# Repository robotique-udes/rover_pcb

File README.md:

# PCB

### How to navigate
This repository contains all the rover PCBs. Projects are sorted by year:

| Year | Surnom du rover | Nom                                                |
|-------------|-----------------|----------------------------------------------------|
| 2024        | T_REX           | Teleoperated Rover for Extraterrestrial Xploration |
| 2025        | NONE            |                                                    |
| 2026        | Wovus           | Rovus but kawaii                                   |
| 2027        | TBD             |                                                    |

### Documentation
All information about the repository rules and PCB specifications can be found in the [rover documentation](https://github.com/robotique-udes/rover_documentation).

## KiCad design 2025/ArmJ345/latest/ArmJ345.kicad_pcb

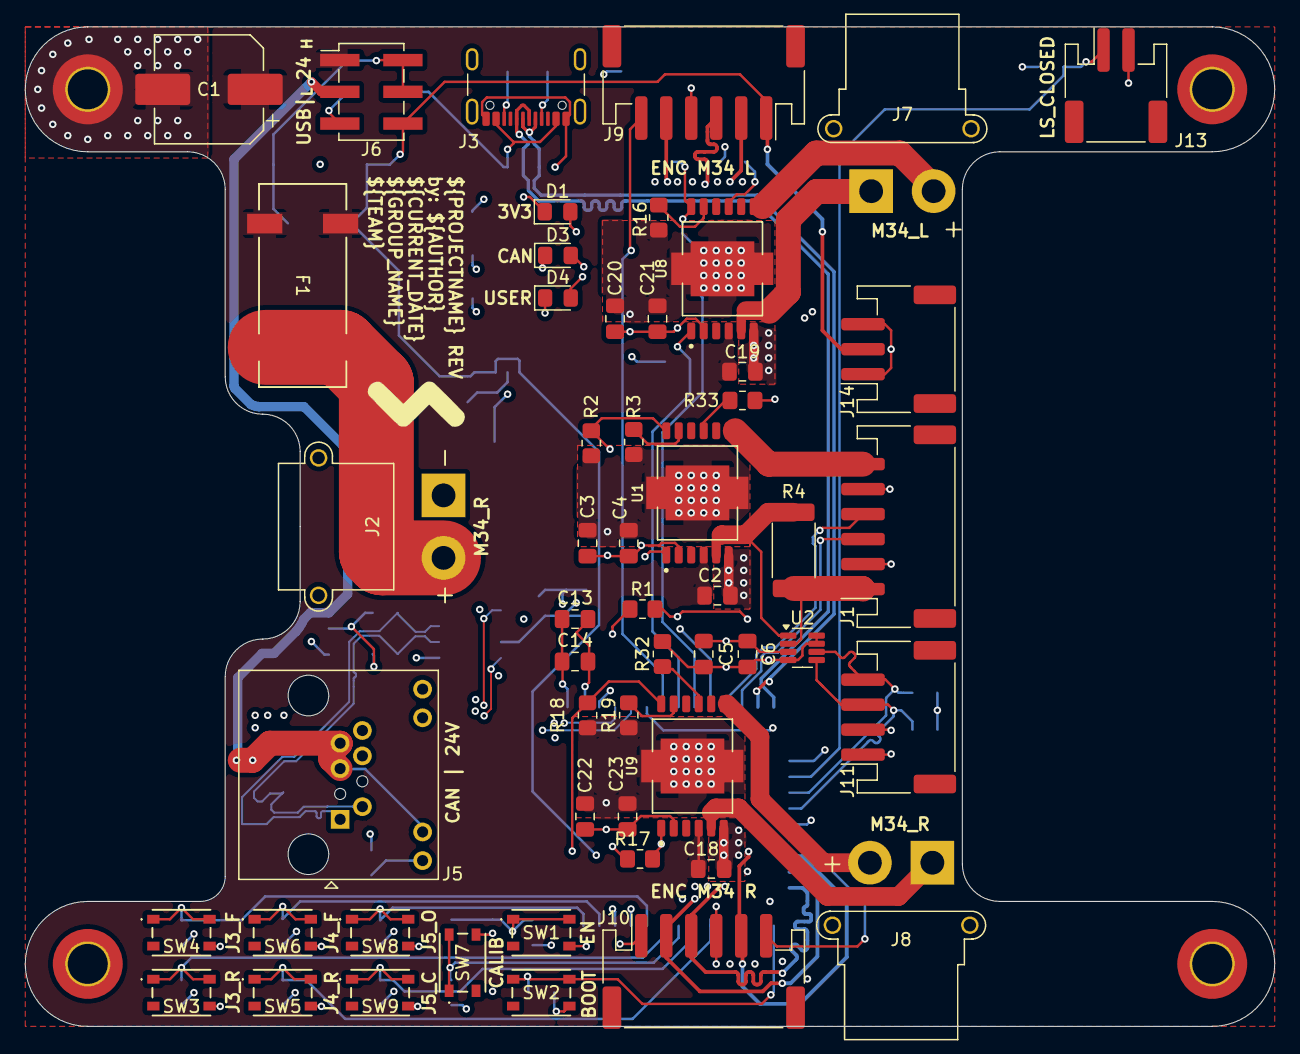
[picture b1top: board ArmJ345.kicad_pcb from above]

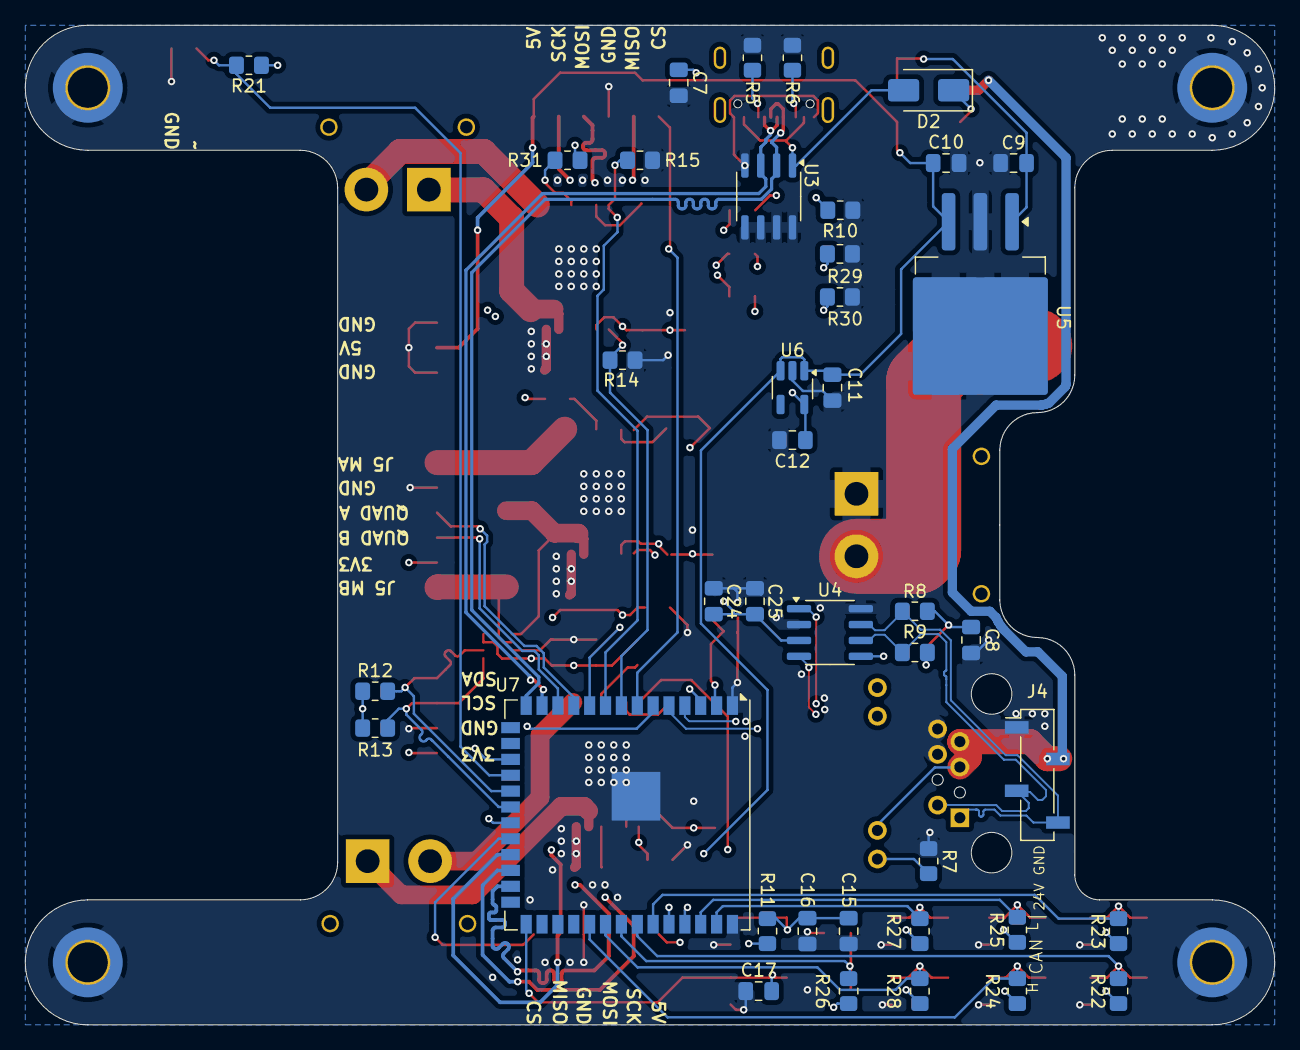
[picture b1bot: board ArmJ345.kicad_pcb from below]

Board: 4 copper layers, 100.0 x 80.0 mm, 97 parts (40 on the bottom side), 63 nets.

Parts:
C1: 470uF; CP_Elec_8x10.5
C2, C4, C6, C14, C16, C17, C18, C19, C21, C23, C25: 100nF; C_0805_2012Metric_Pad1.18x1.45mm_HandSolder
C3, C5, C9, C10, C11, C12, C13, C20, C22, C24: 10uF; C_0805_2012Metric_Pad1.18x1.45mm_HandSolder
C7: 1nF; C_0805_2012Metric_Pad1.18x1.45mm_HandSolder
C8: 4.7nF; C_0805_2012Metric_Pad1.18x1.45mm_HandSolder
C15: 1uF; C_0805_2012Metric_Pad1.18x1.45mm_HandSolder
D1: G; LED_0805_2012Metric_Pad1.15x1.40mm_HandSolder
D2: 40V; D_SMA
D3, D4: B; LED_0805_2012Metric_Pad1.15x1.40mm_HandSolder
F1: 15A; FuseHolder-3588-20
H1, H2, H3, H4: MountingHole_Pad; MountingHole_3.2mm_M3_DIN965_Pad_TopBottom
J1: JST_PH_SB6; JST_PH_S6B-PH-SM4-TB_1x06-1MP_P2.00mm_Horizontal
J2: XT30PW-M; AMASS_XT30PW-M_1x02_P2.50mm_Horizontal
J3: USB_C_USB4105-GF-A; USB_C_Receptacle_GCT_USB4105-xx-A_16P_TopMnt_Horizontal
J4: Conn_01x04_Socket; PinSocket_1x04_P2.54mm_Vertical_SMD_Pin1Left
J5: ETH-RJHSE5081
J6: Conn_02x03_Odd_Even; PinHeader_2x03_P2.54mm_Vertical_SMD
J7, J8: XT30PW-M; AMASS_XT30PW-F_1x02_P2.50mm_Horizontal
J9, J10: JST-PH-S6B; JST_PH_S6B-PH-SM4-TB_1x06-1MP_P2.00mm_Horizontal
J11: Conn_01x04_MountingPin; JST_PH_S4B-PH-SM4-TB_1x04-1MP_P2.00mm_Horizontal
J13: Conn_01x02_MountingPin; JST_PH_S2B-PH-SM4-TB_1x02-1MP_P2.00mm_Horizontal
J14: Conn_01x03_MountingPin; JST_PH_S3B-PH-SM4-TB_1x03-1MP_P2.00mm_Horizontal
R1, R2, R3, R11, R14, R15, R16, R17, R18, R19, R21, R22, R23, R24, R25, R26, R27, R28, R31, R32, R33: 10k; R_0805_2012Metric_Pad1.20x1.40mm_HandSolder
R4: 0.05 (CRA2512-FZ-R050ELF); R_2512_6332Metric_Pad1.40x3.35mm_HandSolder
R5, R6, R7, R10, R29, R30: 5.1k; R_0805_2012Metric_Pad1.20x1.40mm_HandSolder
R8, R9: 60.4; R_0805_2012Metric_Pad1.20x1.40mm_HandSolder
R12, R13: 4.7k; R_0805_2012Metric_Pad1.20x1.40mm_HandSolder
SW1, SW2, SW3, SW4, SW5, SW6, SW7, SW8, SW9: SW-PTS815SJM250SMTRLFS; SW-PTS815 SJM250SMTRLFS
U1, U8, U9: IFX9201SGAUMA1; DRIVE_IFX9201SGAUMA1
U2: CURR_SENSE-INA219AIDCNTG4; SOT-23-8
U3: TVS-SMDB03CE3; SOIC-8_3.9x4.9mm_P1.27mm
U4: SN65HVD232; SOIC-8_3.9x4.9mm_P1.27mm
U5: LDO-LM340SX-5.0/NOPB; TO-263-3_TabPin2
U6: LDO-TLV74033PDBVR; SOT-23-5_HandSoldering
U7: ESP32-S3-WROVER; ESP32-S3-WROOM-1U

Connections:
+3.3V: C3.1, C4.1, C5.1, C6.1, C12.1, C13.1, C14.1, C20.1, C21.1, C22.1, C23.1, C24.1, C25.1, D1.2 (A), J1.2, J11.1, R11.1, R12.1, R13.1, R21.1, R22.1, R23.1, R24.1, R25.1, R26.1, R27.1, R28.1, R31.1, R32.1, R33.1, U1.2 (VSO), U2.4 (VS), U2.7 (A0), U2.8 (A1), U4.3 (VCC), U4.5 (VREF), U6.5 (OUTPUT), U7.2 (3V3), U8.2 (VSO), U9.2 (VSO)
+5V: C10.1, C11.1, J6.6, J9.1, J10.1, J14.2, U5.3 (OUTPUT), U6.1 (INPUT), U6.3 (EN)
+5V_USB: D2.2 (A), J3.A4 (VBUS), J3.A9 (VBUS), J3.B4 (VBUS), J3.B9 (VBUS), U3.1
+24V: C9.1, J6.2, J6.4, U5.1 (INPUT)
+24V_H: C1.1, C2.1, C18.1, C19.1, F1.1, J6.1, U1.4 (VS), U8.4 (VS), U9.4 (VS)
+24V_L: J4.2, J5.5 (Vcc), J5.7 (Vcc), J5.10 (G_L+), J6.3
/Board/drive_j5/M5_A: J1.6, U1.7 (OUT2)
/Board/drive_j5/M5_B: J1.1, R4.2, U2.2 (IN-)
/Board/drive_j5/SENSE_+: R4.1, U1.5 (OUT1), U2.1 (IN+)
/Board/esp32/BOOT_PB: C17.2, SW2.1, SW2.2, U7.27 (IO0-BOOT)
/Board/esp32/CAN_LED: D3.2 (A), U7.17 (IO9)
/Board/esp32/EN_PB: C15.1, C16.2, R11.2, SW1.1, SW1.2, U7.3 (EN)
/Board/esp32/USER_LED: D4.2 (A), U7.6 (IO6)
/Board/external_connections/CC1: J3.A5 (CC1), R5.1
/Board/external_connections/CC2: J3.B5 (CC2), R6.1
CAN_N: J4.3, J5.2 (CANL), R9.1, U4.6 (CANL)
CAN_P: J4.4, J5.1 (CANH), R8.2, U4.7 (CANH)
CAN_RX: U4.4 (RXD), U7.5 (IO5)
CAN_TX: U4.1 (TXD), U7.4 (IO4)
GND: C1.2, C2.2, C3.2, C4.2, C5.2, C6.2, C7.2, C8.2, C9.2, C10.2, C11.2, C12.2, C13.2, C14.2, C15.2, C16.1, C17.1, C18.2, C19.2, C20.2, C21.2, C22.2, C23.2, C24.2, C25.2, H1.1, H2.1, H3.1, H4.1, J1.5, J2.1 (-), J3.A1 (GND), J3.A12 (GND), J3.B1 (GND), J3.B12 (GND), J4.1, J5.6 (GND), J5.8 (GND), J9.4, J10.4, J11.2, J13.2, J14.1, J14.3, R1.2, R2.2, R3.2, R5.2, R6.2, R7.1, R10.1, R14.2, R15.2, R16.2, R17.2, R18.2, R19.2, R29.1, R30.1, SW1.4, SW2.4, SW3.4, SW4.4, SW5.4, SW6.4, SW7.4, SW8.4, SW9.4, U1.6 (GND), U2.3 (GND), U3.4, U3.5, U3.6, U3.7, U3.8, U4.2 (GND), U4.8 (S), U5.2 (GND), U6.2 (GND), U7.1 (GND), U7.40 (GND), U7.41 (GND), U8.6 (GND), U9.6 (GND)
I2C_SCL: J11.3, R13.2, U2.5 (SCL), U7.20 (IO12)
I2C_SDA: J11.4, R12.2, U2.6 (SDA), U7.19 (IO11)
J5_DIR: R1.1, U1.1 (DIR), U7.21 (IO13)
J5_PWM: R2.1, U1.12 (PWM), U7.10 (IO17)
J5_QUAD_A: J1.4, U7.11 (IO18)
J5_QUAD_B: J1.3, U7.12 (IO8)
J34_L_DIR: R14.1, U7.8 (IO15), U8.1 (DIR)
J34_L_PWM: R15.1, U7.9 (IO16), U8.12 (PWM)
J34_R_DIR: R17.1, U7.36 (RXD0), U9.1 (DIR)
J34_R_PWM: R18.1, U7.37 (TXD0), U9.12 (PWM)
M5_LS_CLOSED: J13.1, R21.2, U7.18 (IO10)
unnamed: C8.1, R8.1, R9.2
unnamed: D1.1 (K), R10.2
unnamed: D2.1 (K), J6.5
unnamed: D3.1 (K), R29.2
unnamed: D4.1 (K), R30.2
unnamed: F1.2, J2.2 (+)
unnamed: C7.1, J3.S1 (SHIELD)
unnamed: J5.9 (G_L-), R7.2
unnamed: J7.2 (+), U8.7 (OUT2)
unnamed: J7.1 (-), U8.5 (OUT1)
unnamed: J8.2 (+), U9.7 (OUT2)
unnamed: J8.1 (-), U9.5 (OUT1)
unnamed: R33.2, U1.9 (~CS)
unnamed: R3.1, U1.11 (~EN(DIS))
unnamed: R31.2, U8.9 (~CS)
unnamed: R16.1, U8.11 (~EN(DIS))
unnamed: R32.2, U9.9 (~CS)
unnamed: R19.1, U9.11 (~EN(DIS))
PB_J3_FWD: R23.2, SW4.1, SW4.2, U7.35 (IO42)
PB_J3_REV: R22.2, SW3.1, SW3.2, U7.34 (IO41)
PB_J4_FWD: R25.2, SW6.1, SW6.2, U7.38 (IO2)
PB_J4_REV: R24.2, SW5.1, SW5.2, U7.31 (IO38)
PB_J5_CLOSE: R28.2, SW9.1, SW9.2, U7.32 (IO39)
PB_J5_OPEN: R27.2, SW8.1, SW8.2, U7.39 (IO1)
PB_J34_CALIB: R26.2, SW7.1, SW7.2, U7.33 (IO40)
SPI_CS_ENC_L: J9.6, U7.7 (IO7)
SPI_CS_ENC_R: J10.6, U7.22 (IO14)
SPI_MISO: J9.5, J10.5, U7.23 (IO21)
SPI_MOSI: J9.3, J10.3, U7.25 (IO48)
SPI_SCK: J9.2, J10.2, U7.24 (IO47)
USB_N: J3.A7 (D-), J3.B7 (D-), U3.3, U7.13 (IO19-USB_N)
USB_P: J3.A6 (D+), J3.B6 (D+), U3.2, U7.14 (IO20-USB-P)
